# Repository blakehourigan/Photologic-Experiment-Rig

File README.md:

# Samuelsen Lab Photologic-Experiment-Rig

## Overview
This project was created to enable novel experiments regarding smell and taste in Dr. Chad Samuelsen's research laboratory. The primary improvements that this rig provide include a photologic lick detection mechanism, and a simplified, non-motorized approach to stimulus delivery providing a more reliable experience during experimentation. 

This repository contains all files needed to reproduce a experimental rig of this type, including all 3d models, CNC machining files, code, and circuit design. 

## Features
-  **Data Accuracy** - Important event timing data such as onset, end, duration, onset relative to program start, and onset relative to trial start is measured **on Arduino Mega 2560 device** as these events occur. This ensured event timing results are accurate as viewed in the controller program.
-  **Data Representation** - Licks can be analyzed via a built in lick rasterization plot. This allows for simple visual verification of lick times relative to one another. One can ensure that licks are not occuring too close or too far apart in time. 
-  **Individual Valve / Motor Control** - Users can control each connected valve, opening or closing valves for arbitrary amounts of time. Users can also command the door motor to move up or down at any time. 
-  **Lick/Valve Prohibition** - Lick detection and valve actuation are decoupled events. A lick initiates a valve actuation, however, another lick CANNOT be detected until BOTH the valve has been closed from previous actuation AND tongue has cleared the beam (beam has restored a connection). This helps to avoid licks from occuring too close in succession. Furthermore, a continued beam break does not result in a continuous stream from a valve. A lick initiation will result in a valve opening of the determined length. This will not happen again until beam is restored and broken again. 
-  **Phantom Lick Removal** - Licks that complete in less than 10ms are disregarded and not sent to the controller (PC). This helps avoid invalid licks (due to equipment quirks) being recorded.  
-  **Simplicity** - Significant effort has been expended to ensure that software is easy to install and use. The previous model of using two Arduino boards to control the rig was found to be unnecessary. It was found to be far more effiecient to move to a one Arduino model, simplifying physical setup and communication protocols. 
-  **Speed** - Multiple threads (many cpu workers) are utilized so that GUI is always responsive regardless of logic operations underway at a given moment, without affecting the efficiency of those logic operations. 

### Required Physical Materials

- 1 Arduino Mega 2560
- 1 PC Controller Computer
- 1 Motor Logic Circuit Board
- 1 Experiment Box (3D CAD and CNC files included in this repository)
- 2 - 16 Valves and Cylinders 
 
### Assembly Instructions / Requirements for a Functioning Rig
1. **Rig Controller Code**

   **Documentation for the Rig Controller Code can be found [at this link.](https://blakehourigan.github.io/Photologic-Experiment-Rig/)**
    #### Prerequisites / Dependencies
    To use this program with the Arduino board controlling the rig peripherals (motors, optical sensors, etc) on a Windows machine, you **must** have the Arduino IDE installed. Failing to meet this dependency will result in the Arduino boards failure to connect to the controlling computer. 
    
    #### Windows Installation 
    To install the program on windows, there are two options. 
    
    1. **Exe Installer File** - To simplify this portion of the rig assembly / installation, a simple .exe installer has been provided. It can be found [here](https://github.com/blakehourigan/Photologic-Experiment-Rig/releases/tag/v1.0).
    
    2. **Running the Source Code** - For those that would rather run the program via source code, the process for getting the source code up and running can be found below.
        1. **Install Python 3.12** - This program was developed with Python version 3.12. This program is NOT guaranteed to work with any versions other than Python3.12. It can be installed [here](https://www.python.org/downloads/release/python-3120/).
        2. **Clone this repository locally on your computer** - Either by using git clone on your machine, or by clicking the 'code' dropdown on the homepage of this Github repo and downloading the .zip file, download this repository onto your machine.
        3. **Setup the Virtual Environment** - Once you have the repo locally on your machine, navigate to the controller code directory at `Photologic-Experiment-Rig\Code\Photologic Rig Main Application Code`. Once here, you can setup a virtual environment that will contain all depencies for the program by running the following command in a terminal window at this directory: `python -m venv venv'. This may take a few moments.
        4. **Activate the Environment** - Once the virtual environment is setup, you can activate it by running the following command.
            - **Windows** -> `venv\Scripts\Activate`
            - **Linux** -> `source venv/bin/activate `
        6. **Install the Dependencies** - This program is dependent on many external libraries to function properly. Under the 'Photologic Rig Main Application Code' directory, you will also find a file called requirements.txt. It contains all depencencies and their versions in a simple text file. You can install all of these dependencies at once by running the command `pip install -r requirements.txt`.
        7. **Run the Program** - You are now ready to run the controller program. Locate the file 'main.py' under the /src directory and run it by running the command `python main.py`, the program should now startup.

    #### Running the Program on Linux-based Systems
    There is no installation file for linux-based systems. Follow the 'Running the Source Code' steps described above.

    #### Building an Executable for a New Version of the Program
    For those that create new versions of the program to better suit their needs or to fix bugs that will undoubdedly arise through the usage of this program, a [Github Gist](https://gist.github.com/blakehourigan/5e176f2600446a793547babff372299c) has been put together detailing the steps you can take to create a new executable file and installer that will make installation/distribution of the program much simpler. 
    
3. **Arduino Code**
    #### Prerequisites / Dependencies
    To upload this code, you will need either the arduino-cli or the Arduino IDE. The Arduino IDE will be easiest to work with and can be found [here](https://www.arduino.cc/en/software).

    On Windows machines, the Arduino IDE is an optional package in the control software Exe installer discussed above.

    If you choose to use the Arduino IDE, you must follow these steps to ensure smooth upload of this code to the Arduino, and proper communication between the Arduino and the control software.
    #### IDE Configuration and Code Upload
    1. Once the Arduino IDE is installed, open the IDE with the Arduino Mega 2560 board connected to your PC. Your PC will recognize the board and the packages that it needs to install to communicate with it. There will be multiple pop-up windows asking if you would like to install drivers for this board. You **must** click install on all of these pop-ups. If you do not see these pop-ups and have used your Arduino board previously, you may have these packages already installed, try moving to the next step. 
    2. The code used for the Arduino in this project has one external dependency that must be fulfilled. This external dependency is the **AccelStepper** library by Mike McCauley. The version in use at the time of writing is version 1.64. You will need to install this version in the IDE. To do this, look for the library icon on the left hand side of the Arduino IDE window. It is the third button down. Once clicked, a slide-out window with the heading 'library manager' will open with a search box at the top. Click inside of the search bar and enter 'AccelStepper'. The first result should be the one you are looking for. Click the box filled with the version number (something like 1.64), and look for version 1.64. Click on this version, then click install, it should install rather quickly. Now you can now exit the library manager.
    3. Now, the Arduino code may be uploaded to the board. In the top left hand corner, click 'File', then 'Open', and search for the ArduinoCode directory in the Photologic-Experiment-Rig structure. The file you are looking for will be found at `Photologic-Experiment-Rig/Code/ArduinoCode/ArduinoCode.ino`. Locate this .ino file and double click on it to select it.
    4. Once this file is open in the IDE, ensure that your board is recognized and selected in the IDE by clicking the dropdown menu just below the 'help' section of the top bar. Here you will see any Arduino boards recognized by the PC. Select your Arduino Mega 2560 board.
    5. With the file open and your board selected, press the green upload button. It is the arrow that looks like this: '-->', the second button of three in the top left hand side of your screen. This will just take a moment, and you will see a 'Done Uploading' message in the bottom right of your screen if it completes successfully.

       **NOTE** - If you see lots of red messages and this code does not upload successfully, please make absolutely sure you installed the 'ArduinoStepper' library and that the board is connected **and** selected. You might try the board selection dropdown again to make sure of this. If this does not work, try disconnecting and reconnecting the board, and restarting your PC. 
    7. At this point your Arduino board and your PC are ready to communicate with each other for your experiments. 
 
4. **3D Printing:**

   Under contruction

5. **Machining:**   

   Under Contruction 

6. **Assembly:** 

   Under contruction

7. **Optical Fiber Setup:**   

   Under contruction

8. **Circuitry:** 

   Under contruction 

### Configuration

how to configure the system once assembled.

## Usage
A **SOP** (Standard Operating Procedure) for using this rig in an experiment can be found [here]().

## Navigating the Directory Structure
Each subdirectory in this project contains a README that explains the structure of the files contained within.

## License

This project is licensed under the MIT License - see LICENSE.txt for details.

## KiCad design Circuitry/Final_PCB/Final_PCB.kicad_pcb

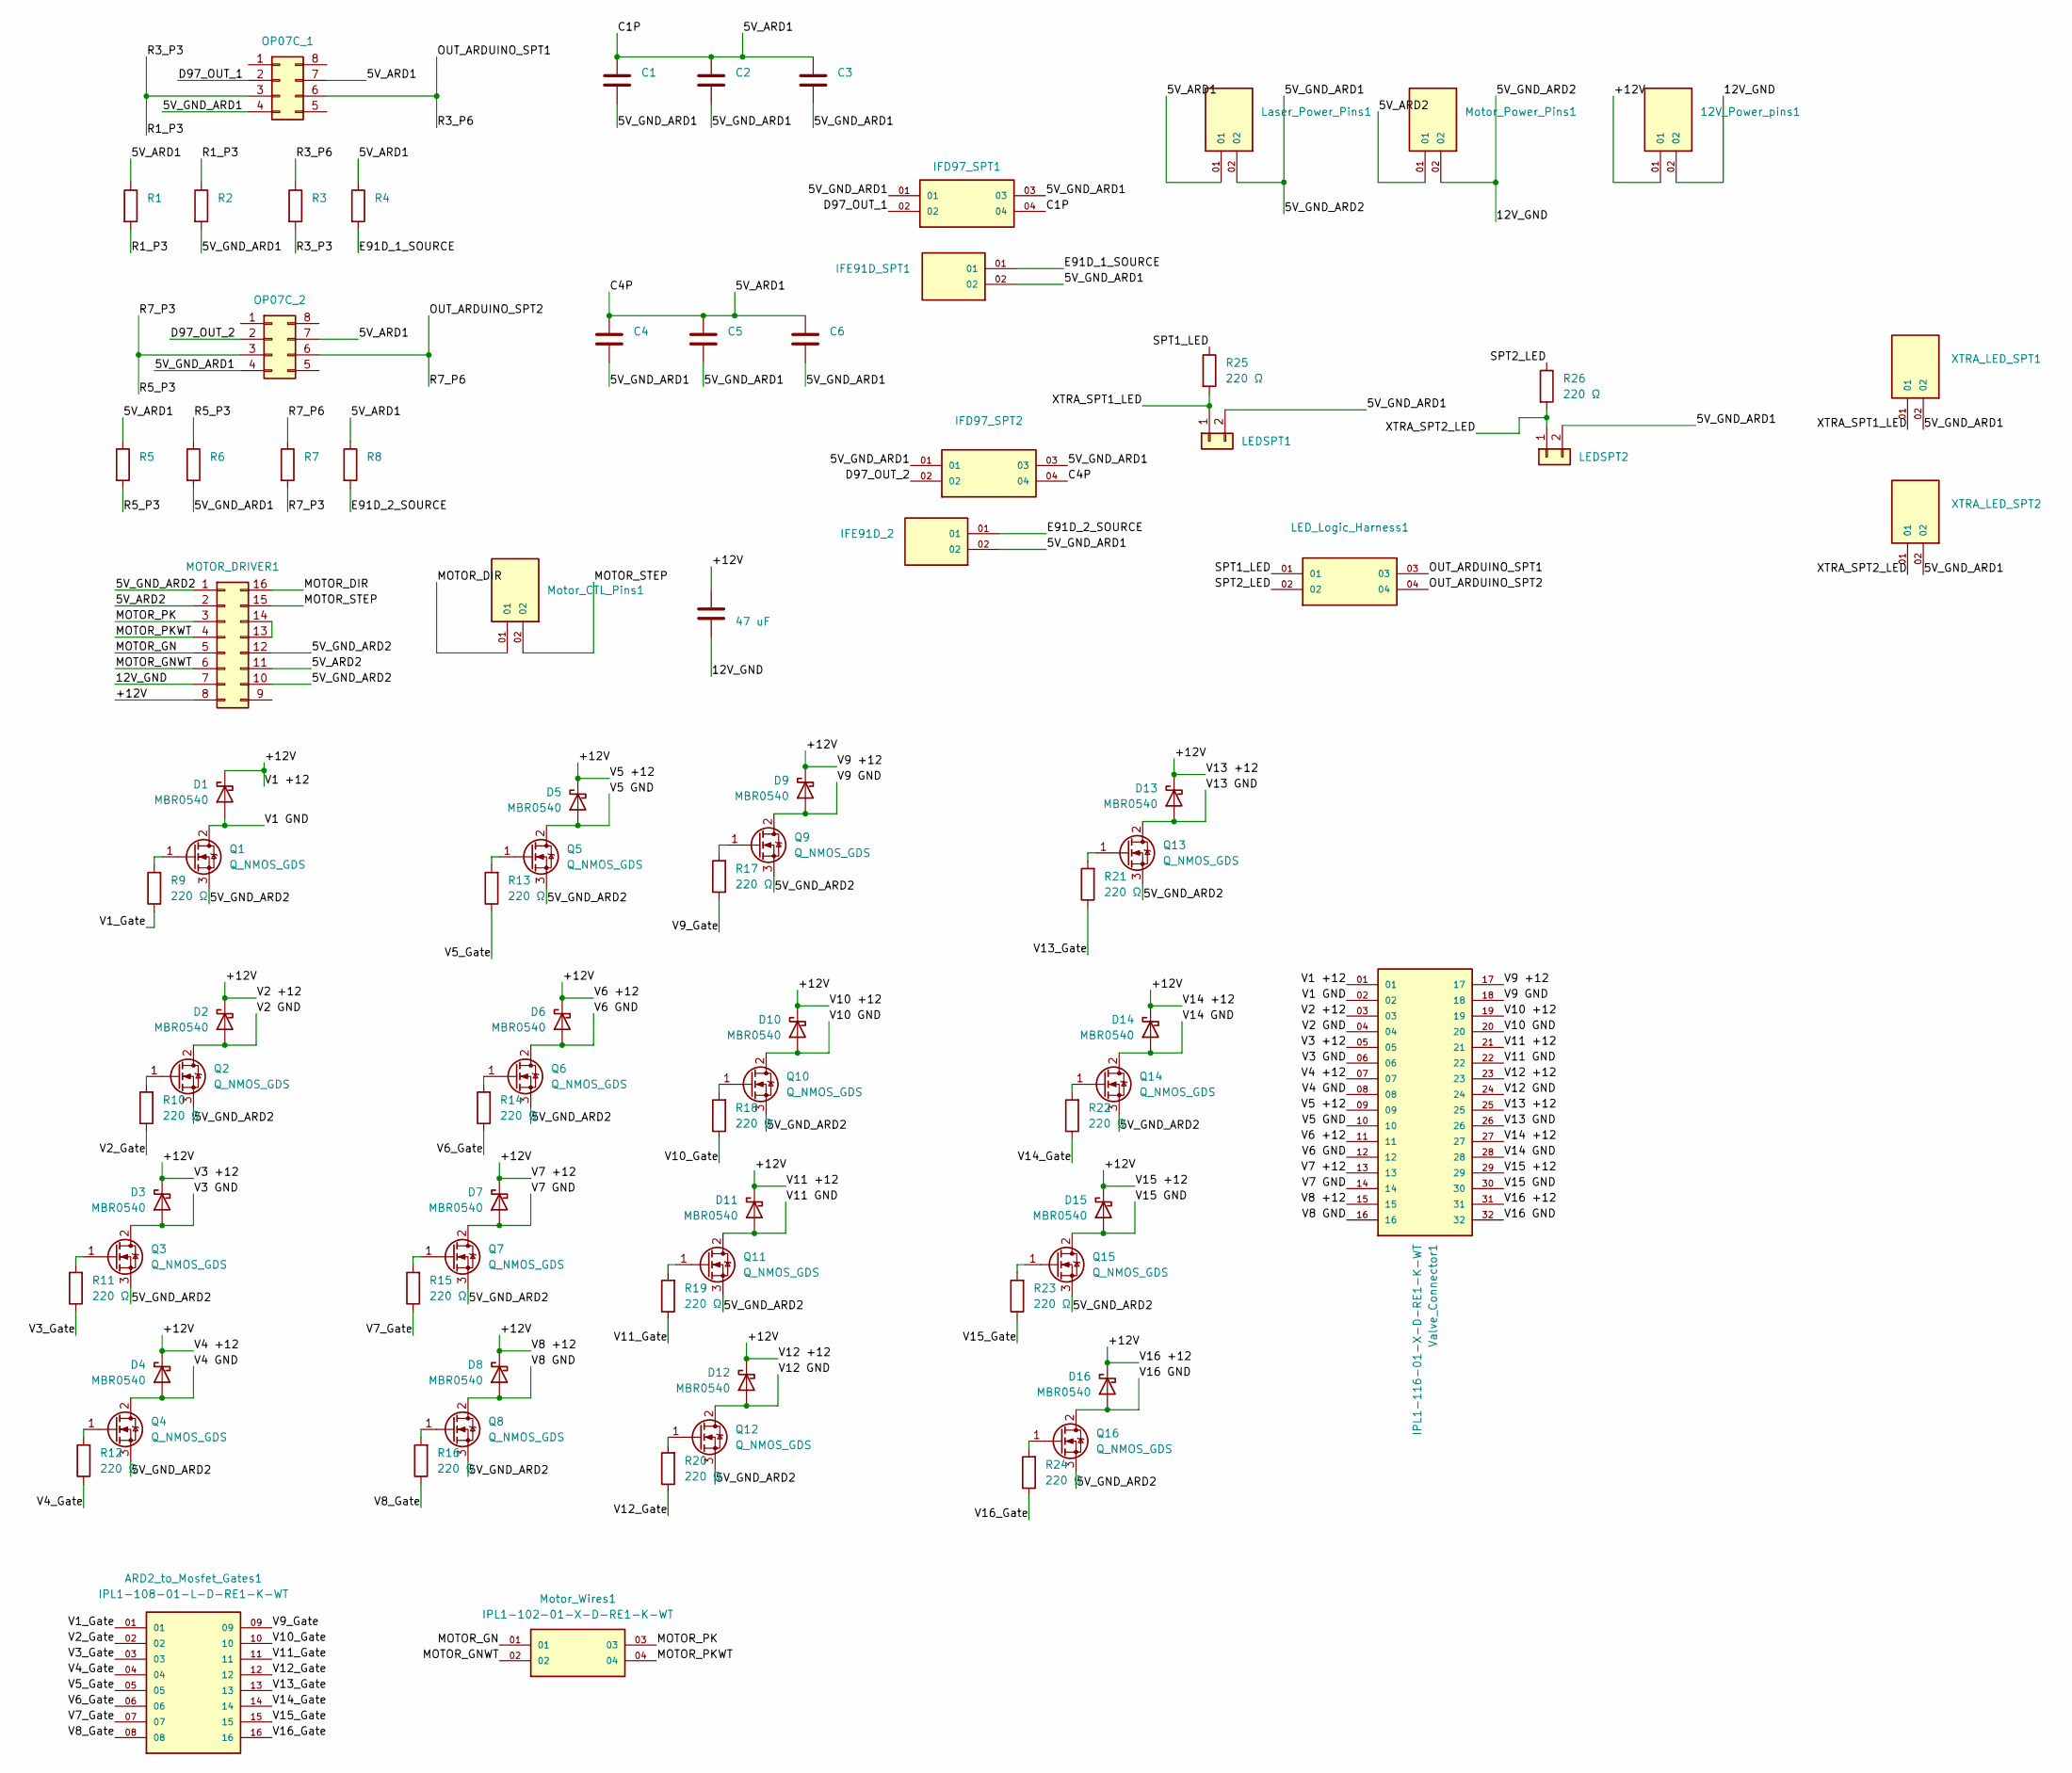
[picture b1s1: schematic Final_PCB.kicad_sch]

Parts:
12V_Power_pins1: IPL1-102-01-L-S-RE1-K-WT; SAMTEC_IPL1-102-01-L-S-RE1-K-WT
ARD2_to_Mosfet_Gates1: IPL1-108-01-L-D-RE1-K-WT; SAMTEC_IPL1-108-01-L-D-RE1-K-WT
C1, C3, C4, C6: 1 uF; CP_Radial_D5.0mm_P2.00mm
C2, C5: 10 uF; CP_Radial_D10.0mm_P5.00mm
C7: 47 uF; CP_Radial_D4.0mm_P2.00mm
D1, D2, D3, D4, D5, D6, D7, D8, D9, D10, D11, D12, D13, D14, D15, D16: MBR0540; D_DO-15_P15.24mm_Horizontal
IFD97_SPT1, IFD97_SPT2: IPL1-102-01-X-D-RE1-K-WT; SAMTEC_IPL1-102-01-X-D-RE1-K-WT; PARTREV A
IFE91D_2, IFE91D_SPT1: IPL1-102-01-L-S-RE1-K-WT; SAMTEC_IPL1-102-01-L-S-RE1-K-WT
LEDSPT1, LEDSPT2: Conn_01x02; R_Axial_DIN0204_L3.6mm_D1.6mm_P2.54mm_Vertical
LED_Logic_Harness1: IPL1-102-01-X-D-RE1-K-WT; SAMTEC_IPL1-102-01-X-D-RE1-K-WT; PARTREV A
Laser_Power_Pins1: IPL1-102-01-L-S-RE1-K-WT; SAMTEC_IPL1-102-01-L-S-RE1-K-WT
MOTOR_DRIVER1: Conn_02x08_Counter_Clockwise; Motor_Driver_A4988
Motor_CTL_Pins1: IPL1-102-01-L-S-RE1-K-WT; SAMTEC_IPL1-102-01-L-S-RE1-K-WT
Motor_Power_Pins1: IPL1-102-01-L-S-RE1-K-WT; SAMTEC_IPL1-102-01-L-S-RE1-K-WT
Motor_Wires1: IPL1-102-01-X-D-RE1-K-WT; SAMTEC_IPL1-102-01-X-D-RE1-K-WT; PARTREV A
OP07C_1, OP07C_2: Conn_02x04_Counter_Clockwise; DIP-8_W7.62mm
Q1, Q2, Q3, Q4, Q5, Q6, Q7, Q8, Q9, Q10, Q11, Q12, Q13, Q14, Q15, Q16: Q_NMOS_GDS; TO-220-3_Vertical
R1, R5: 2.4K Ω; R_Axial_DIN0207_L6.3mm_D2.5mm_P7.62mm_Horizontal
R2, R6: 1K Ω; R_Axial_DIN0207_L6.3mm_D2.5mm_P7.62mm_Horizontal
R3, R7: 47K Ω; R_Axial_DIN0207_L6.3mm_D2.5mm_P7.62mm_Horizontal
R4, R8: 56 Ω; R_Axial_DIN0207_L6.3mm_D2.5mm_P7.62mm_Horizontal
R9, R10, R11, R12, R13, R14, R15, R16, R17, R18, R19, R20, R21, R22, R23, R24, R25, R26: 220 Ω; R_Axial_DIN0204_L3.6mm_D1.6mm_P7.62mm_Horizontal
Valve_Connector1: IPL1-116-01-X-D-RE1-K-WT; SAMTEC_IPL1-116-01-X-D-RE1-K-WT
XTRA_LED_SPT1, XTRA_LED_SPT2: IPL1-102-01-L-S-RE1-K-WT; SAMTEC_IPL1-102-01-L-S-RE1-K-WT

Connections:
/+12V: 12V_Power_pins1.01, C7.1, D1.1 (K), D2.1 (K), D3.1 (K), D4.1 (K), D5.1 (K), D6.1 (K), D7.1 (K), D8.1 (K), D9.1 (K), D10.1 (K), D11.1 (K), D12.1 (K), D13.1 (K), D14.1 (K), D15.1 (K), D16.1 (K), MOTOR_DRIVER1.8, Valve_Connector1.01, Valve_Connector1.03, Valve_Connector1.05, Valve_Connector1.07, Valve_Connector1.09, Valve_Connector1.11, Valve_Connector1.13, Valve_Connector1.15, Valve_Connector1.17, Valve_Connector1.19, Valve_Connector1.21, Valve_Connector1.23, Valve_Connector1.25, Valve_Connector1.27, Valve_Connector1.29, Valve_Connector1.31
/D97_OUT_1: IFD97_SPT1.02, OP07C_1.2
/D97_OUT_2: IFD97_SPT2.02, OP07C_2.2
/E91D_1_SOURCE: IFE91D_SPT1.01, R4.2
/E91D_2_SOURCE: IFE91D_2.01, R8.2
/GND: 12V_Power_pins1.02, C1.2, C2.2, C3.2, C4.2, C5.2, C6.2, C7.2, IFD97_SPT1.01, IFD97_SPT1.03, IFD97_SPT2.01, IFD97_SPT2.03, IFE91D_2.02, IFE91D_SPT1.02, LEDSPT1.2, LEDSPT2.2, Laser_Power_Pins1.02, MOTOR_DRIVER1.1, MOTOR_DRIVER1.7, MOTOR_DRIVER1.10, MOTOR_DRIVER1.12, Motor_Power_Pins1.02, OP07C_1.4, OP07C_2.4, Q1.3 (S), Q2.3 (S), Q3.3 (S), Q4.3 (S), Q5.3 (S), Q6.3 (S), Q7.3 (S), Q8.3 (S), Q9.3 (S), Q10.3 (S), Q11.3 (S), Q12.3 (S), Q13.3 (S), Q14.3 (S), Q15.3 (S), Q16.3 (S), R2.2, R6.2, XTRA_LED_SPT1.02, XTRA_LED_SPT2.02; also elsewhere on the board
/MOTOR_DIR: MOTOR_DRIVER1.16, Motor_CTL_Pins1.01
/MOTOR_GN: MOTOR_DRIVER1.5, Motor_Wires1.01
/MOTOR_GNWT: MOTOR_DRIVER1.6, Motor_Wires1.02
/MOTOR_PK: MOTOR_DRIVER1.3, Motor_Wires1.03
/MOTOR_PKWT: MOTOR_DRIVER1.4, Motor_Wires1.04
/MOTOR_STEP: MOTOR_DRIVER1.15, Motor_CTL_Pins1.02
/OUT_ARDUINO_SPT1: LED_Logic_Harness1.03, OP07C_1.6, R3.1
/OUT_ARDUINO_SPT2: LED_Logic_Harness1.04, OP07C_2.6, R7.1
/SPT1_LED: LED_Logic_Harness1.01, R25.1
/SPT2_LED: LED_Logic_Harness1.02, R26.1
/V1 GND: D1.2 (A), Q1.2 (D), Valve_Connector1.02
/V1_Gate: ARD2_to_Mosfet_Gates1.01, R9.1; also elsewhere on the board
/V2 GND: D2.2 (A), Q2.2 (D), Valve_Connector1.04
/V2_Gate: ARD2_to_Mosfet_Gates1.02, R10.1; also elsewhere on the board
/V3 GND: D3.2 (A), Q3.2 (D), Valve_Connector1.06
/V3_Gate: ARD2_to_Mosfet_Gates1.03, R11.1; also elsewhere on the board
/V4 GND: D4.2 (A), Q4.2 (D), Valve_Connector1.08
/V4_Gate: ARD2_to_Mosfet_Gates1.04, R12.1; also elsewhere on the board
/V5 GND: D5.2 (A), Q5.2 (D), Valve_Connector1.10
/V5_Gate: ARD2_to_Mosfet_Gates1.05, R13.1; also elsewhere on the board
/V6 GND: D6.2 (A), Q6.2 (D), Valve_Connector1.12
/V6_Gate: ARD2_to_Mosfet_Gates1.06, R14.1; also elsewhere on the board
/V7 GND: D7.2 (A), Q7.2 (D), Valve_Connector1.14
/V7_Gate: ARD2_to_Mosfet_Gates1.07, R15.1; also elsewhere on the board
/V8 GND: D8.2 (A), Q8.2 (D), Valve_Connector1.16
/V8_Gate: ARD2_to_Mosfet_Gates1.08, R16.1; also elsewhere on the board
/V9 GND: D9.2 (A), Q9.2 (D), Valve_Connector1.18
/V9_Gate: ARD2_to_Mosfet_Gates1.09, R17.1; also elsewhere on the board
/V10 GND: D10.2 (A), Q10.2 (D), Valve_Connector1.20
/V10_Gate: ARD2_to_Mosfet_Gates1.10, R18.1; also elsewhere on the board
/V11 GND: D11.2 (A), Q11.2 (D), Valve_Connector1.22
/V11_Gate: ARD2_to_Mosfet_Gates1.11, R19.1; also elsewhere on the board
/V12 GND: D12.2 (A), Q12.2 (D), Valve_Connector1.24
/V12_Gate: ARD2_to_Mosfet_Gates1.12, R20.1; also elsewhere on the board
/V13 GND: D13.2 (A), Q13.2 (D), Valve_Connector1.26
/V13_Gate: ARD2_to_Mosfet_Gates1.13, R21.1; also elsewhere on the board
/V14 GND: D14.2 (A), Q14.2 (D), Valve_Connector1.28
/V14_Gate: ARD2_to_Mosfet_Gates1.14, R22.1; also elsewhere on the board
/V15 GND: D15.2 (A), Q15.2 (D), Valve_Connector1.30
/V15_Gate: ARD2_to_Mosfet_Gates1.15, R23.1; also elsewhere on the board
/V16 GND: D16.2 (A), Q16.2 (D), Valve_Connector1.32
/V16_Gate: ARD2_to_Mosfet_Gates1.16, R24.1; also elsewhere on the board
/XTRA_SPT1_LED: LEDSPT1.1, R25.2, XTRA_LED_SPT1.01
/XTRA_SPT2_LED: LEDSPT2.1, R26.2, XTRA_LED_SPT2.01
/side_one_pin_3: OP07C_1.3, R1.2, R2.1, R3.2
/side_two_pin_three: OP07C_2.3, R5.2, R6.1, R7.2
unnamed: MOTOR_DRIVER1.13, MOTOR_DRIVER1.14
unnamed: Q1.1 (G), R9.2
unnamed: Q2.1 (G), R10.2
unnamed: Q3.1 (G), R11.2
unnamed: Q4.1 (G), R12.2
unnamed: Q5.1 (G), R13.2
unnamed: Q6.1 (G), R14.2
unnamed: Q7.1 (G), R15.2
unnamed: Q8.1 (G), R16.2
unnamed: Q9.1 (G), R17.2
unnamed: Q10.1 (G), R18.2
unnamed: Q11.1 (G), R19.2
unnamed: Q12.1 (G), R20.2
unnamed: Q13.1 (G), R21.2
unnamed: Q14.1 (G), R22.2
unnamed: Q15.1 (G), R23.2
unnamed: Q16.1 (G), R24.2

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
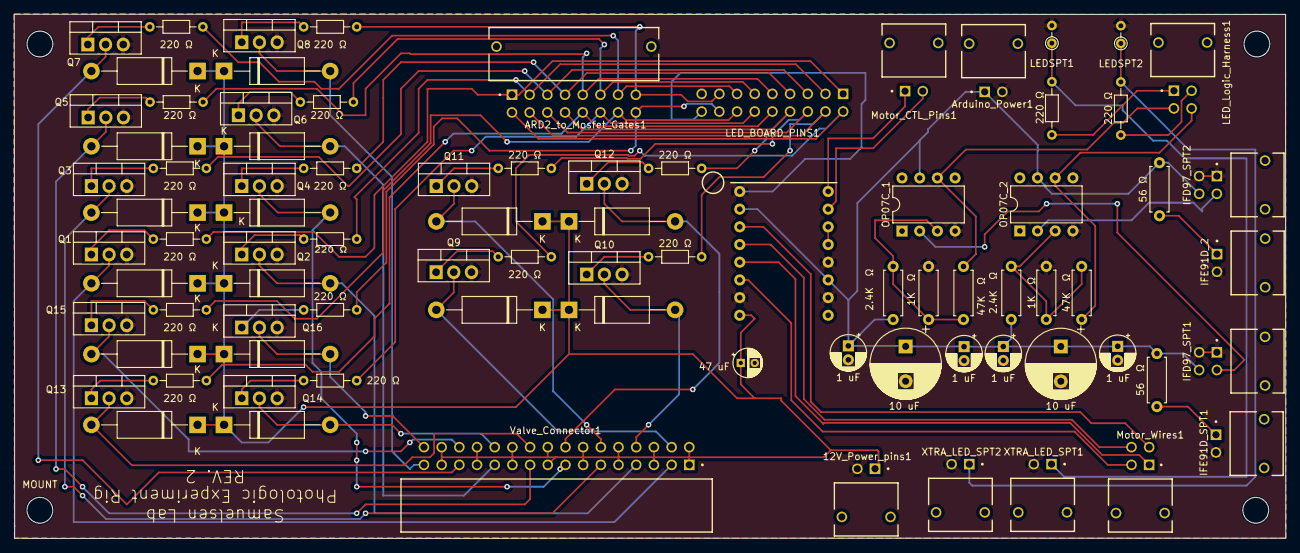
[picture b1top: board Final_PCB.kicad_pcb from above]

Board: 2 copper layers, 182.6 x 75.3 mm, 85 parts (1 on the bottom side), 70 nets.

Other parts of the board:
Arduino_Power1: IPL1-102-01-L-S-RE1-K-WT; SAMTEC_IPL1-102-01-L-S-RE1-K-WT
LED_BOARD_PINS1: IPL1-108-01-L-D-RE1-K-WT; SAMTEC_IPL1-109-01-L-D-RE1-K
MOUNT: MountingHole_3.7mm

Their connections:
/GND: Arduino_Power1.02, LED_BOARD_PINS1.18; also elsewhere on the board
/V1_Gate: LED_BOARD_PINS1.01; also elsewhere on the board
/V2_Gate: LED_BOARD_PINS1.02; also elsewhere on the board
/V3_Gate: LED_BOARD_PINS1.03; also elsewhere on the board
/V4_Gate: LED_BOARD_PINS1.04; also elsewhere on the board
/V5_Gate: LED_BOARD_PINS1.05; also elsewhere on the board
/V6_Gate: LED_BOARD_PINS1.06; also elsewhere on the board
/V7_Gate: LED_BOARD_PINS1.07; also elsewhere on the board
/V8_Gate: LED_BOARD_PINS1.08; also elsewhere on the board
/V9_Gate: LED_BOARD_PINS1.10; also elsewhere on the board
/V10_Gate: LED_BOARD_PINS1.11; also elsewhere on the board
/V11_Gate: LED_BOARD_PINS1.12; also elsewhere on the board
/V12_Gate: LED_BOARD_PINS1.13; also elsewhere on the board
/V13_Gate: LED_BOARD_PINS1.14; also elsewhere on the board
/V14_Gate: LED_BOARD_PINS1.15; also elsewhere on the board
/V15_Gate: LED_BOARD_PINS1.16; also elsewhere on the board
/V16_Gate: LED_BOARD_PINS1.17; also elsewhere on the board

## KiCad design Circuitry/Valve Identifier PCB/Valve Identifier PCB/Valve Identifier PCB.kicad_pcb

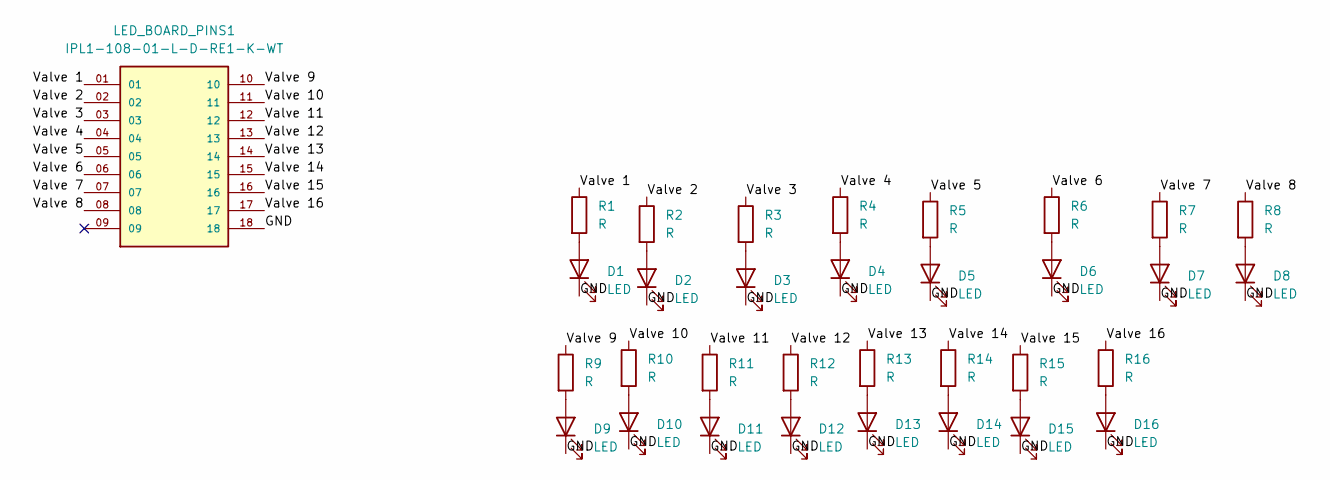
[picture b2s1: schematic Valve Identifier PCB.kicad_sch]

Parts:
D1, D2, D3, D4, D5, D6, D7, D8, D9, D10, D11, D12, D13, D14, D15, D16: LED; R_Axial_DIN0204_L3.6mm_D1.6mm_P2.54mm_Vertical
LED_BOARD_PINS1: IPL1-108-01-L-D-RE1-K-WT; SAMTEC_IPL1-109-01-L-D-RE1-K; PARTREV A
R1, R2, R3, R4, R5, R6, R7, R8, R9, R10, R11, R12, R13, R14, R15, R16: R; R_Axial_DIN0204_L3.6mm_D1.6mm_P5.08mm_Horizontal

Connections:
/GND: D1.1 (K), D2.1 (K), D3.1 (K), D4.1 (K), D5.1 (K), D6.1 (K), D7.1 (K), D8.1 (K), D9.1 (K), D10.1 (K), D11.1 (K), D12.1 (K), D13.1 (K), D14.1 (K), D15.1 (K), D16.1 (K), LED_BOARD_PINS1.18
/Valve 1: LED_BOARD_PINS1.01, R1.1
/Valve 2: LED_BOARD_PINS1.02, R2.1
/Valve 3: LED_BOARD_PINS1.03, R3.1
/Valve 4: LED_BOARD_PINS1.04, R4.1
/Valve 5: LED_BOARD_PINS1.05, R5.1
/Valve 6: LED_BOARD_PINS1.06, R6.1
/Valve 7: LED_BOARD_PINS1.07, R7.1
/Valve 8: LED_BOARD_PINS1.08, R8.1
/Valve 9: LED_BOARD_PINS1.10, R9.1
/Valve 10: LED_BOARD_PINS1.11, R10.1
/Valve 11: LED_BOARD_PINS1.12, R11.1
/Valve 12: LED_BOARD_PINS1.13, R12.1
/Valve 13: LED_BOARD_PINS1.14, R13.1
/Valve 14: LED_BOARD_PINS1.15, R14.1
/Valve 15: LED_BOARD_PINS1.16, R15.1
/Valve 16: LED_BOARD_PINS1.17, R16.1
unnamed: D1.2 (A), R1.2
unnamed: D2.2 (A), R2.2
unnamed: D3.2 (A), R3.2
unnamed: D4.2 (A), R4.2
unnamed: D5.2 (A), R5.2
unnamed: D6.2 (A), R6.2
unnamed: D7.2 (A), R7.2
unnamed: D8.2 (A), R8.2
unnamed: D9.2 (A), R9.2
unnamed: D10.2 (A), R10.2
unnamed: D11.2 (A), R11.2
unnamed: D12.2 (A), R12.2
unnamed: D13.2 (A), R13.2
unnamed: D14.2 (A), R14.2
unnamed: D15.2 (A), R15.2
unnamed: D16.2 (A), R16.2

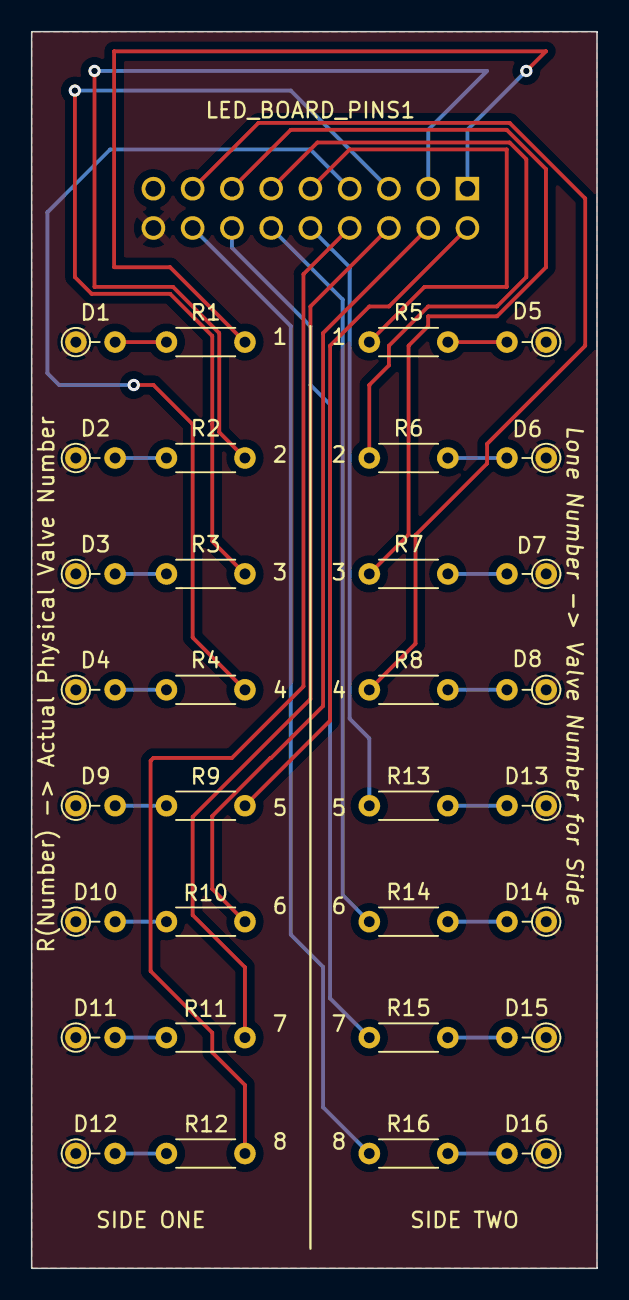
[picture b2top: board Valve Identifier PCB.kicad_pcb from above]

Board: 2 copper layers, 36.6 x 80.0 mm, 33 parts (1 on the bottom side), 33 nets.

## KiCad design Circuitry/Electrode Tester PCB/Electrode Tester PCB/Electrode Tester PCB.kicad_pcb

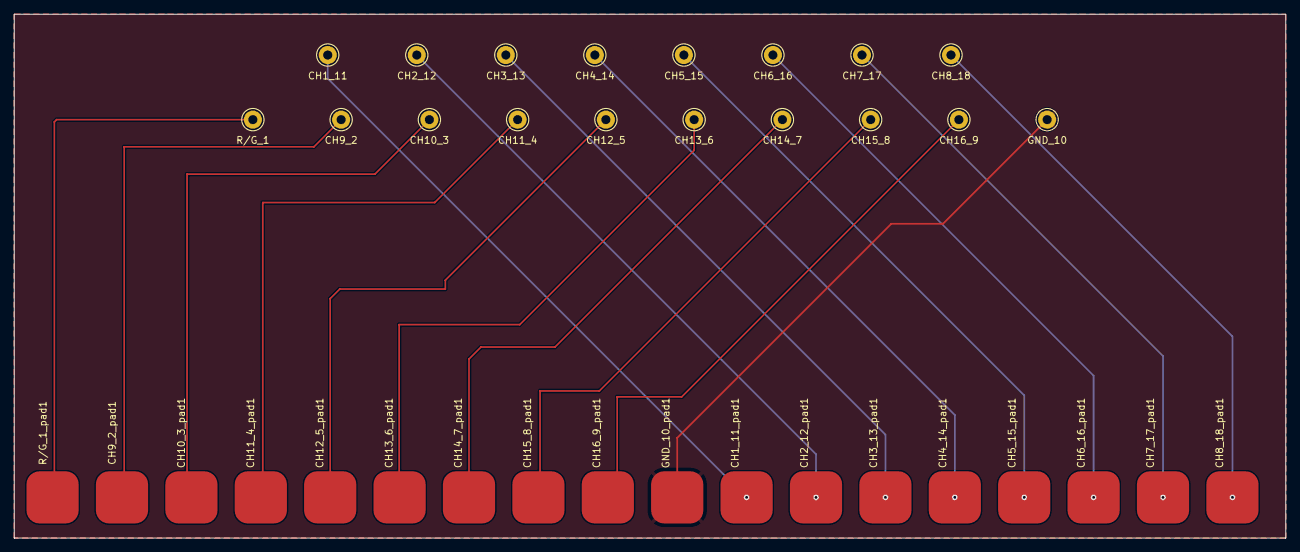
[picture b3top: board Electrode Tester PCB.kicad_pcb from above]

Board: 2 copper layers, 182.5 x 75.2 mm, 36 parts (0 on the bottom side), 18 nets.

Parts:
CH1_11, CH2_12, CH3_13, CH4_14, CH5_15, CH6_16, CH7_17, CH8_18, CH9_2, CH10_3, CH11_4, CH12_5, CH13_6, CH14_7, CH15_8, CH16_9: Conn_01x01_Pin; Pin_D1.3mm_L11.0mm
CH1_11_pad1, CH2_12_pad1, CH3_13_pad1, CH4_14_pad1, CH5_15_pad1, CH6_16_pad1, CH7_17_pad1, CH8_18_pad1, CH9_2_pad1, CH10_3_pad1, CH11_4_pad1, CH12_5_pad1, CH13_6_pad1, CH14_7_pad1, CH15_8_pad1, CH16_9_pad1: Conn_01x01_Pin; Test Pad
GND_10: Conn_01x01_Pin; Pin_D1.3mm_L11.0mm
GND_10_pad1: Conn_01x01_Pin; Test Pad
R/G_1: Conn_01x01_Pin; Pin_D1.3mm_L11.0mm
R/G_1_pad1: Conn_01x01_Pin; Test Pad

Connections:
/CH1 - 11: CH1_11.1, CH1_11_pad1.1
/CH2 - 12: CH2_12.1, CH2_12_pad1.1
/CH3 - 13: CH3_13.1, CH3_13_pad1.1
/CH4 - 14: CH4_14.1, CH4_14_pad1.1
/CH5 - 15: CH5_15.1, CH5_15_pad1.1
/CH6 - 16: CH6_16.1, CH6_16_pad1.1
/CH7 - 17: CH7_17.1, CH7_17_pad1.1
/CH8 - 18: CH8_18.1, CH8_18_pad1.1
/CH9 - 2: CH9_2.1, CH9_2_pad1.1
/CH10 - 3: CH10_3.1, CH10_3_pad1.1
/CH11 - 4: CH11_4.1, CH11_4_pad1.1
/CH12 - 5: CH12_5.1, CH12_5_pad1.1
/CH13 - 6: CH13_6.1, CH13_6_pad1.1
/CH14 - 7: CH14_7.1, CH14_7_pad1.1
/CH15 - 8: CH15_8.1, CH15_8_pad1.1
/CH16 - 9: CH16_9.1, CH16_9_pad1.1
/GND - 10: GND_10.1, GND_10_pad1.1
/R/G - 1: R/G_1.1, R/G_1_pad1.1

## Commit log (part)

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2024-03-15 update python valve testing code & motor ard valve test code
2024-03-15 fix ordering of valve test
2024-03-15 update valve testing code
2024-03-15 update motor code
    almost got it
2024-03-15 update valve test code
2024-03-15 valve testing updates
2024-03-15 update test code
2024-03-15 print line
2024-03-15 fixed valve test code
2024-03-15 VALVE TEST CODE WORKS!!!
2024-03-15 minor updates
2024-03-18 update motor test eeprom with new values
2024-03-19 updated motor code
2024-03-21 finalizing motor code (v1)
2024-03-21 circuitry update
2024-03-22 refactor of motor interface and comm code
2024-03-22 fixing bugs
2024-03-22 fixing motor code testing bugs
2024-03-25 update schedule sending code
2024-03-25 schedule updates
2024-03-25 update schedule send code
2024-03-25 schedule code efficiency greatly improved
2024-03-25 update duration updater
2024-03-26 finalizing valve testing
2024-03-26 splitting eeprom code
2024-03-26 fix door not closing when licking simultaniously
2024-03-26 data management bug fix
2024-03-26 update motor code, diagnosing door issues
2024-03-26 Everything seems to be working :)
2024-03-26 Laser detection made more accurate
2024-03-26 removing unnecessary timer from laser code
2024-03-26 gui fixes
2024-03-26 investigating slowdowns
2024-03-27 efficiency updates
2024-03-27 fixing adding to df errors
2024-03-27 move clock updates back to the main thread
2024-03-27 Finalized test code
2024-03-27 valve identifier board
2024-03-28 modularizing motor arduino code
2024-04-01 motor timestamps
2024-04-01 motor stamping code
2024-04-01 program control gui bug fix, time stamp data collection fix
2024-04-03 time stamp data update
2024-04-03 trial start and end times append update
2024-04-03 fix motor timestamp bugs
2024-04-03 update motor stamping code
2024-04-03 new run data
2024-04-03 update the way stimulus is added to df and timestamp code
2024-04-03 sorting licks df in licks window
2024-04-04 update timestamp code
2024-04-04 new data
2024-04-04 timestamp updates
2024-04-05 acquiring more timestamps
2024-04-05 licks window update and motor schedule bug fix
2024-04-05 various updates and bug fixes XD
2024-04-05 fixed timestamps not populating
2024-04-05 raster
2024-04-05 add delay until door is fully opened for ttc
2024-04-05 fix lick data header mismatch
2024-04-05 raster plot implementation take 1
2024-04-05 zeroing the licks
2024-04-05 raster updates
2024-04-05 modify raster plot x axis & bttn name
2024-04-09 test code
2024-04-11 new linear motion carrier
2024-04-11 spout faceplate cnc
2024-04-11 spout arms final
2024-04-12 motor ino updates
2024-04-12 code updates & data
2024-04-14 cage model updates
2024-04-15 sliding bracket 2.0
2024-04-15 new sliding brackets
2024-04-15 updates slides
2024-04-16 faceplate stencil nc file
2024-04-22 motor wire holder
2024-04-22 vacuum tube mosture capture
2024-04-25 File updates
2024-04-26 File Structure Overhaul / Cleaning up the file base
2024-04-26 More File Structure Updates
2024-04-26 one more file structure thing
2024-04-26 code updates
2024-04-29 sided rasterized data plots fix
2024-04-29 raster plot updates
2024-04-30 Drain valves logic improved
2024-04-30 debug valve opening issues
2024-04-30 removing reversal of last four valve control bits
2024-04-30 valve control window finishing touches
2024-04-30 restructure calls to send info to arduinos
2024-04-30 restore old motor code
2024-04-30 A RESET BUTTON!
2024-04-30 restart button fixes
2024-04-30 prime valves functionality restore
2024-05-02 Updating test code
2024-05-03 change defaults
2024-05-11 new refactor
2024-05-11 updated how valves are activated
2024-05-12 couple of minor bugs
2024-05-13 fixed testing code to better align with new valve switch code
2024-05-13 auto save on close on exp completion
2024-05-14 logging kind of rules???
    how come nobody ever told me about this?
2024-05-14 various minor bugs
2024-05-14 finally fixed it yeesh
2024-05-17 revise valve_duration communication
2024-05-17 new valve duration communication working
2024-05-17 splitting the valve durations
2024-05-18 tracked down testing bugs
2024-05-24 valve testing window gui updates
2025-02-19 fixing the diaster area
2025-02-20 more cleaning
2025-02-22 getting there
2025-02-24 most gui elements complete
2025-02-25 begin state machine work
2025-02-28 state machine updates
2025-02-28 more state machine improvements, ard data relocation
2025-02-28 making sure require. are up-to-date
2025-02-28 move requirements back to its home
2025-03-05 clean up, make motor arduino code more efficient
2025-03-05 clean motor readme
2025-03-05 restructure motor ard code
2025-03-05 markdown readme motor code
2025-03-06 restore point for potential chaos
2025-03-07 unify arduino code into single arduino
2025-03-08 arduino code unification complete
2025-03-09 finish data recording on ard -> controller
2025-03-12 finish basic testing logic, abort logic, test gui
2025-03-12 manual timing adjustments
2025-03-12 logs
2025-03-12 fix valve test window conflicts
2025-03-13 remove vectors from arduino code
2025-03-13 remove random file
2025-03-13 update exp_init readme
2025-03-13 finish testing window
2025-03-14 add test duration change confirmation window
2025-03-14 fix the value used in amt_dispensed_per_lick to the tkinter var 'actuations'
2025-03-14 prime function COMPLETE!
2025-03-14 various github issues resolved, ready for windows testing
2025-03-14 set default save dir to /data_outputs
2025-03-14 bind window destroy action valve testing to withdraw to avoid error
2025-03-15 Delete Code/Photologic Rig Main Application Code/logfiles/14:22:58 - 2025-03-14 experiment log
    windows doesn't like : in files
2025-03-15 Delete Code/Photologic Rig Main Application Code/logfiles/14:23:46 - 2025-03-14 experiment log
    windows doesn't like ':'
2025-03-15 Delete Code/Photologic Rig Main Application Code/logfiles/14:23:7 - 2025-03-14 experiment log
    windows doesn't like ':'
2025-03-15 Delete Code/Photologic Rig Main Application Code/logfiles/14:24:17 - 2025-03-14 experiment log
    windows doesn't like ':'
2025-03-15 update file structure for exe format
2025-03-15 finished installer
2025-03-15 Bump pillow in /Code/Photologic Rig Main Application Code
    Bumps [pillow](https://github.com/python-pillow/Pillow) from 10.1.0 to 10.3.0.
    - [Release notes](https://github.com/python-pillow/Pillow/releases)
    - [Changelog](https://github.com/python-pillow/Pillow/blob/main/CHANGES.rst)
    - [Commits](https://github.com/python-pillow/Pillow/compare/10.1.0...10.3.0)
    ---
    updated-dependencies:
2025-03-16 new requirements
2025-03-16 update gitignore
2025-03-16 more gitignore
2025-03-16 remove main.dist for real!
2025-03-16 ignore arduino installer used for distributino
2025-03-16 readme for rig-file in /src
2025-03-16 main controller code readme
2025-03-16 move readme
2025-03-16 arduino dir struct. readme
2025-03-16 add installer script
2025-03-16 fix arduino not connecting on program reset
2025-03-16 fix valve testing / priming mode switch error gh issue #19
2025-03-16 modify gui resize code
2025-03-17 fix gui oversized bug
2025-03-17 fix issue #18 arduino not connected crashes program
2025-03-17 resolve issue #25
2025-03-17 resolve gh issue #17, band-aid solution to issue #26
2025-03-18 fix issues #20, #26
2025-03-19 update experiment defaults
2025-03-20 fix valve test confirm gui #28, remove pathlib dependent code #27, documentation dir
2025-03-20 update docs
2025-03-20 fix issue where windows wouldn't show again after closing
2025-03-20 iss updates
2025-03-20 fix program reset button for windows
2025-03-25 Create pdoc
2025-03-25 Update pdoc
2025-03-25 requirements.txt & docs
2025-03-25 Rename pdoc to pdocs.yml
2025-03-25 docs action test
2025-03-25 init.py at src root
2025-03-25 rm init.py at src root
2025-03-25 docs dir for code docs
2025-03-26 debugging github action
2025-03-26 add docs
2025-03-26 add missing docs
2025-03-26 main docs
2025-03-26 app_logic.py docs
2025-03-26 update pdocs
2025-03-26 update app_logic pdocs
2025-03-26 app_logic.py docs, app_logic class instance variables reduction updates
2025-03-26 finalize app_logic.py docs
2025-03-27 complete docs for main_gui
2025-03-27 start arduino docs, valve_testing docs
2025-03-28 arduino docs
2025-03-28 event_window docs
2025-03-28 experiment ctl window
2025-03-28 gui common docs
2025-03-28 finish view docs except for valve testing
2025-03-29 fix gui_common docs
2025-03-29 manual_time_adjustment docs
2025-03-29 valve_test_window docs
2025-03-29 docs finished
2025-04-04 add software user guide
2025-04-08 constants for valve times in valve_testing
2025-04-10 add new mainboard design, led breakout board design kicad
2025-04-10 finalize new pcb design, flipped connector location for the LED breakout board
2025-04-10 fix breakout board connector orientation
2025-04-10 update led text placement
2025-04-14 updated solidworks parts
    update for heat inserts
2025-04-15 collimator
2025-04-16 easy print tops
2025-04-16 spout faceplate cnc file
2025-04-16 new c2d spout faceplate
2025-04-16 MOAR STEPS
2025-04-16 new c2d top acryllic piece
2025-04-16 separate back and sides
2025-04-16 new c2d SIDE acryllic piece
2025-04-17 faceplate for damaged leg
2025-04-17 update new faceplate
2025-04-17 main faceplate damaged legs small holes
2025-04-17 new top c2d
2025-04-18 modify spout faceplate c2d
2025-04-18 back wall c2d add cnc
2025-04-18 update back wall c2d
2025-04-22 motorized aluminum door cnc c2d file
2025-04-22 slow two sides c2d
2025-04-22 two back walls slow
2025-04-22 two tops c2d file
2025-04-23 slim down acryllic walls for wiggle room
2025-04-24 two faceplates slow for box with damaged leg
2025-04-24 only right faceplate edge c2d
2025-04-24 main faceplate c2d with tape
2025-04-24 main faceplate standard leg hole cutouts c2d
2025-04-25 fill full aluminum sheet with other parts such as spout faceplate and door
2025-04-28 step files for PCBs, shells for boards
2025-04-28 step updates, stls
2025-04-30 start cnc machine docs
2025-04-30 update cnc machine docs
2025-05-02 model updates
2025-05-02 step swivel mount
2025-05-06 new spout faceplate
2025-05-13 main faceplate 3 port rig c2d
2025-07-02 fix issue #30. update IR state management, add 90ms timeout for new lick onset.
2025-07-02 add capacitive touch functionality to ArduinoCode
2025-07-03 fix capacitive lick enable code. only read during sample time.
2025-07-03 update rig assembly files
2025-07-03 test
2025-07-03 add and disable ability to click valve once on trial start
2025-07-03 reconfigure rig assembly files structure
2025-07-11 match capacitive code to photologic arduino code
2025-07-23 implement low-pass filter, serial comms code for capacitive circuit
2025-07-28 new vacuum splitter
2025-07-28 Update Top Lock Keeper STL and remove temp file
    Replaced Top Lock Keeper Assemblies.STL with a new version and deleted the temporary ~$Top Lock Keeper Assemblies.SLDPRT file.
2025-12-12 STEP file for latches
